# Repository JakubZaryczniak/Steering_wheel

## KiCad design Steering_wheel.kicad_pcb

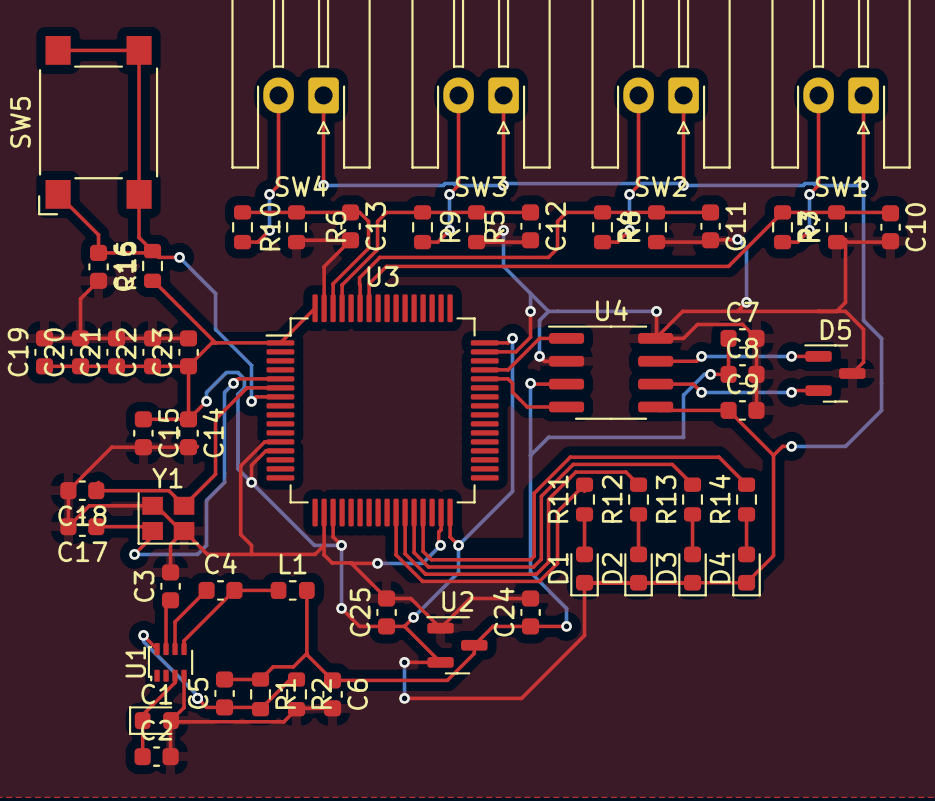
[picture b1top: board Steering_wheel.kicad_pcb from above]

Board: 2 copper layers, 56 parts (0 on the bottom side), 31 nets.

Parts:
C1: 10u; LED_0603_1608Metric
C2, C4, C19, C20, C21, C22: 100n; C_0603_1608Metric
C3: 33n; C_0603_1608Metric
C5: 47p; C_0603_1608Metric
C6: 47u; C_0603_1608Metric
C7, C9, C10, C11, C12, C13, C16: 100nF; C_0603_1608Metric
C8: 1uF; C_0603_1608Metric
C14: 10n; C_0603_1608Metric
C15, C23: 1u; C_0603_1608Metric
C17, C18: 10pF; C_0603_1608Metric
C24: 100u; C_0603_1608Metric
C25: 10u; C_0603_1608Metric
D1, D2, D3, D4: LED; LED_0603_1608Metric
D5: PESD2CAN.215; SOT-23
L1: 10u; L_0603_1608Metric
R1: 52k3; R_0603_1608Metric
R2, R7, R8, R9, R10, R15: 10k; R_0603_1608Metric
R3, R4, R5, R6, R11, R12, R13, R14: 1k; R_0603_1608Metric
SW1, SW2, SW3, SW4: SW_Push; JST_XH_S2B-XH-A-1_1x02_P2.50mm_Horizontal
SW5: SW_SMD; SW_SPST_Omron_B3FS-100xP
U1: TPS62933; SOT-583-8
U2: Regulator_Linear_LM1117-3.3; SOT-23
U3: STM32L4P5RETx; LQFP-64_10x10mm_P0.5mm
U4: ATA6561-GAQW-N; SOIC-8_3.9x4.9mm_P1.27mm
Y1: Crystal_GND24; Crystal_SMD_2520-4Pin_2.5x2.0mm

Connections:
+3V3: C9.1, C14.1, C15.1, C19.1, C20.1, C21.1, C22.1, C23.1, C25.1, D1.1 (K), D2.1 (K), D3.1 (K), D4.1 (K), R15.1, SW1.1, SW2.1, SW3.1, SW4.1, U2.2 (VO), U3.1 (VBAT), U3.13 (VDDA), U3.19 (VDD), U3.32 (VDD), U3.48 (VDDUSB), U3.64 (VDD), U4.5 (VIO)
+5V: C5.2, C6.1, C7.1, C8.1, C24.1, L1.2, R1.1, U2.3 (VI), U4.3 (VDD)
+24V: C1.1, C2.1, U1.3 (VIN)
/CAN+: D5.1 (A1), U4.7 (CANH)
/CAN-: D5.2 (A2), U4.6 (CANL)
/CAN_RX: U3.44 (PA11), U4.4 (RXD)
/CAN_TX: U3.45 (PA12), U4.1 (TXD)
/Crystal_IN: C17.1, U3.5 (PH0), Y1.1
/Crystal_Out: C18.1, U3.6 (PH1), Y1.3
/DebugLED1: R11.2, U3.26 (PB0)
/DebugLED2: R12.2, U3.27 (PB1)
/DebugLED3: R13.2, U3.28 (PB2)
/DebugLED4: R14.2, U3.29 (PB10)
/NRST: C16.1, R15.2, SW5.1 (A), SW5.2 (A), U3.7 (NRST)
/SW1: C10.1, R3.1, R7.2, U3.58 (PB6)
/SW2: C11.1, R4.1, R8.2, U3.59 (PB7)
/SW3: C12.1, R5.1, R9.2, U3.61 (PB8)
/SW4: C13.1, R6.1, R10.2, U3.62 (PB9)
GND: C1.2, C2.2, C3.2, C6.2, C7.2, C8.2, C9.2, C10.2, C11.2, C12.2, C13.2, C14.2, C15.2, C16.2, C17.2, C18.2, C19.2, C20.2, C21.2, C22.2, C23.2, C24.2, C25.2, D5.3 (common), R2.2, R7.1, R8.1, R9.1, R10.1, U1.4 (GND), U2.1 (GND), U3.12 (VSSA), U3.18 (VSS), U3.31 (VSS), U3.47 (VSS), U3.60 (PH3), U3.63 (VSS), U4.2 (VSS), U4.8 (S), Y1.2, Y1.4
unnamed: D1.2 (A), R11.1
unnamed: D2.2 (A), R12.1
unnamed: D3.2 (A), R13.1
unnamed: D4.2 (A), R14.1
unnamed: R3.2, SW1.2
unnamed: R4.2, SW2.2
unnamed: R5.2, SW3.2
unnamed: R6.2, SW4.2
unnamed: C4.1, U1.6 (BST)
unnamed: C5.1, R1.2, R2.1, U1.8 (FB)
unnamed: C3.1, U1.7 (SS)
unnamed: C4.2, L1.1, U1.5 (SW)
